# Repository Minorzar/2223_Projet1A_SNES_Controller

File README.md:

# SNES Project (Controller)

This is the repository of the SNES project carried out at ENSEA by the promotion of 2025.

In the first year, as part of a three-month project, we will attempt to create our own version of the SNES controller. The aim will be to complete the controller ourselves, both in terms of hardware and software, while adding features that were not present on the original controller. However, this is only the first part of our SNES project, as we'll be continuing the project next year, this time focusing on the console itself. As such, this repository will probably only contain files relevant to the controller.

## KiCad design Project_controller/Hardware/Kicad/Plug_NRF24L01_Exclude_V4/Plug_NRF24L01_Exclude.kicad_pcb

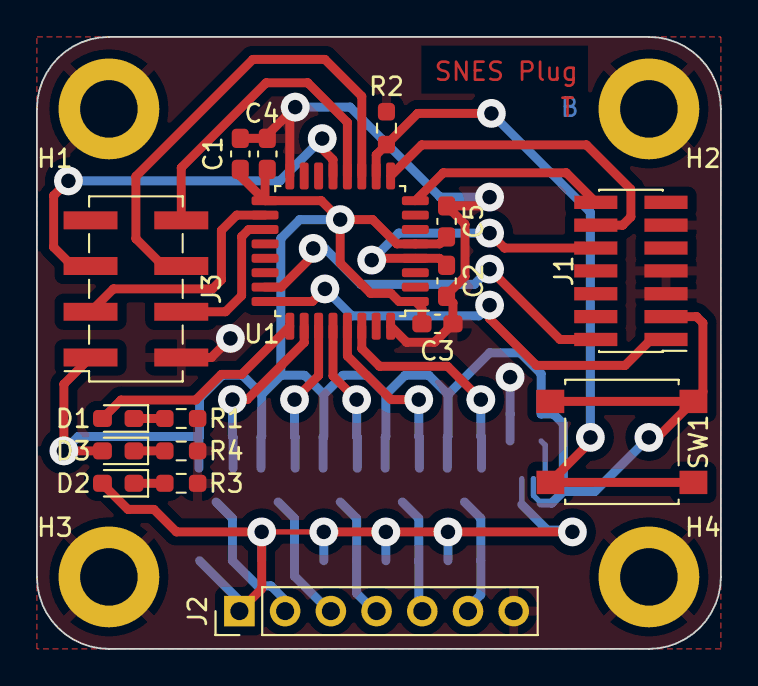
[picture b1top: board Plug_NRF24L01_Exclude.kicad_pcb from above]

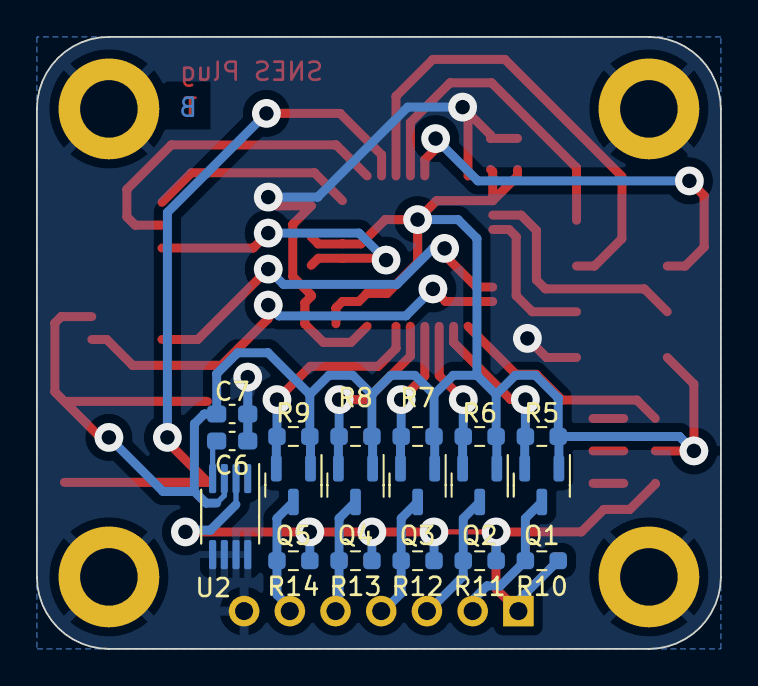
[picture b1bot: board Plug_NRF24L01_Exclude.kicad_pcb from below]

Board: 2 copper layers, 38.0 x 34.0 mm, 39 parts (18 on the bottom side), 29 nets.

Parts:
C1: 10u; C_0603_1608Metric_Pad1.08x0.95mm_HandSolder
C2, C3, C4, C5: 100n; C_0603_1608Metric_Pad1.08x0.95mm_HandSolder
C6: 470p; C_0603_1608Metric_Pad1.08x0.95mm_HandSolder
C7: 2.2u; C_0603_1608Metric_Pad1.08x0.95mm_HandSolder
D1, D2: LED_Small; D_0603_1608Metric_Pad1.05x0.95mm_HandSolder
D3: LED; D_0603_1608Metric_Pad1.05x0.95mm_HandSolder
H1, H2, H3, H4: MountingHole_Pad; MountingHole_3.2mm_M3_DIN965_Pad
J1: Conn_02x07_Odd_Even; PinHeader_2x07_P1.27mm_Vertical_SMD
J2: Conn_01x07_Socket; PinHeader_1x07_P2.54mm_Vertical
J3: Conn_01x08_Socket; PinSocket_2x04_P2.54mm_Vertical_SMD
Q1, Q2, Q3, Q4, Q5: 2N7002; SOT-23
R1, R3, R4: 1k; R_0603_1608Metric_Pad0.98x0.95mm_HandSolder
R2, R5, R6, R7, R8, R9, R10, R11, R12, R13, R14: 10k; R_0603_1608Metric_Pad0.98x0.95mm_HandSolder
SW1: SW_SPST; SW_SPST_B3S-1000
U1: STM32L412KBTx; LQFP-32_7x7mm_P0.8mm
U2: MIC5219-3.3YMM; MSOP-8_3x3mm_P0.65mm

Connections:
+3.3V: C1.1, C3.1, C4.1, C5.1, C7.1, D3.2 (A), J1.3, J3.1, Q1.1 (G), Q2.1 (G), Q3.1 (G), Q4.1 (G), Q5.1 (G), R5.1, R6.1, R7.1, R8.1, R9.1, SW1.2 (B), U1.1 (VDD), U1.5 (VDDA), U1.17 (VDD), U2.3 (OUT)
+5V: D2.2 (A), J2.1, R10.1, R11.1, R12.1, R13.1, R14.1, U2.2 (IN)
Appairing_Btn: R2.1, SW1.1 (A), U1.10 (PA4)
Chip_Enable: J3.4, U1.19 (PA9)
Data_Clock_SNES: J2.2, Q1.3 (D), R10.2
Data_Clock_STM32: Q1.2 (S), R5.2, U1.26 (PB3)
Data_Latch_SNES: J2.3, Q2.3 (D), R11.2
Data_Latch_STM32: Q2.2 (S), R6.2, U1.27 (PB4)
GND: C1.2, C2.1, C3.2, C4.2, C5.2, C6.2, C7.2, H1.1, H2.1, H3.1, H4.1, J1.5, J1.7, J1.11, J2.7, J3.2, R1.2, R2.2, R3.2, R4.2, U1.16 (VSS), U1.32 (VSS), U2.5 (GND), U2.6 (GND), U2.7 (GND), U2.8 (GND)
IOBit_SNES: J2.6, Q5.3 (D), R14.2
IOBit_STM32: Q5.2 (S), R9.2, U1.30 (PB7)
NRST: C2.2, J1.10, U1.4 (NRST)
unnamed: D1.1 (K), R1.1
unnamed: D2.1 (K), R3.1
unnamed: D3.1 (K), R4.1
unnamed: C6.1, U2.4 (BP)
SPI_Chip_Select: J3.3, U1.18 (PA8)
SPI_Clock: J3.6, U1.11 (PA5)
SPI_Digital_Input: J3.8, U1.12 (PA6)
SPI_Digital_Output: J3.5, U1.13 (PA7)
SWDCK: J1.1, U1.24 (PA14)
SWDIO: J1.2, U1.23 (PA13)
Serial_Data1_SNES: J2.4, Q3.3 (D), R12.2
Serial_Data1_STM32: Q3.2 (S), R7.2, U1.28 (PB5)
Serial_Data2_SNES: J2.5, Q4.3 (D), R13.2
Serial_Data2_STM32: Q4.2 (S), R8.2, U1.29 (PB6)
Status_LED: D1.2 (A), U1.25 (PA15)
USART2_RX: J1.12, U1.9 (PA3)
USART2_TX: J1.14, U1.8 (PA2)

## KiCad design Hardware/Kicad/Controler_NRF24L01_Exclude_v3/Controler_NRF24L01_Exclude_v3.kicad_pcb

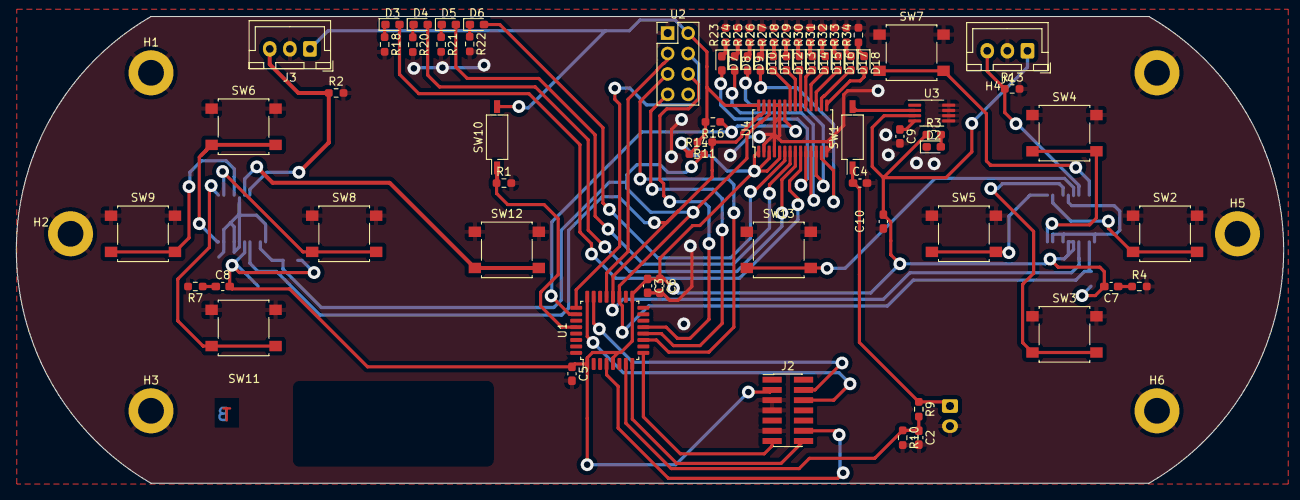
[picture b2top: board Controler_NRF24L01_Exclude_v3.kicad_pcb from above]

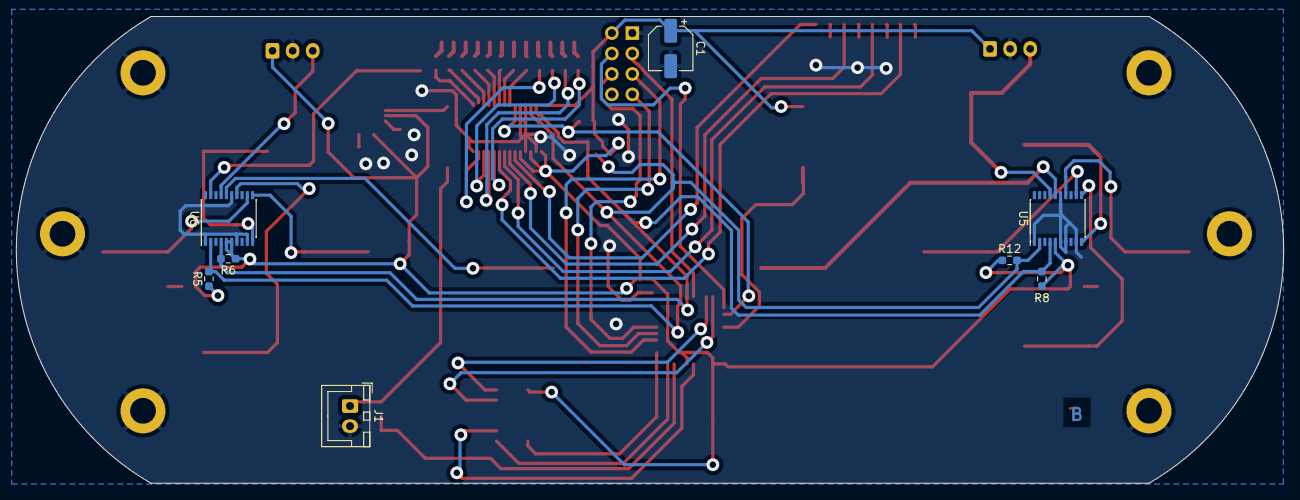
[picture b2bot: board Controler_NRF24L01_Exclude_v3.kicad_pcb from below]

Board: 2 copper layers, 157.4 x 58.0 mm, 87 parts (8 on the bottom side), 68 nets.

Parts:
C1: 22uF; CP_Elec_5x5.4
C2: 1nF; C_0603_1608Metric_Pad1.08x0.95mm_HandSolder
C3, C5: 100n; C_0603_1608Metric_Pad1.08x0.95mm_HandSolder
C4: 1u; C_0603_1608Metric_Pad1.08x0.95mm_HandSolder
C6: 10u; C_0603_1608Metric_Pad1.08x0.95mm_HandSolder
C7, C8, C10: 100nF; C_0603_1608Metric_Pad1.08x0.95mm_HandSolder
C9: 470p; C_0603_1608Metric_Pad1.08x0.95mm_HandSolder
D2: LED_Small; LED_0603_1608Metric_Pad1.05x0.95mm_HandSolder
D3: G1; LED_0603_1608Metric_Pad1.05x0.95mm_HandSolder
D4: G2; LED_0603_1608Metric_Pad1.05x0.95mm_HandSolder
D5: G3; LED_0603_1608Metric_Pad1.05x0.95mm_HandSolder
D6: G4; LED_0603_1608Metric_Pad1.05x0.95mm_HandSolder
D7: G5; LED_0603_1608Metric_Pad1.05x0.95mm_HandSolder
D8: G6; LED_0603_1608Metric_Pad1.05x0.95mm_HandSolder
D9: G7; LED_0603_1608Metric_Pad1.05x0.95mm_HandSolder
D10: G8; LED_0603_1608Metric_Pad1.05x0.95mm_HandSolder
D11: O1; LED_0603_1608Metric_Pad1.05x0.95mm_HandSolder
D12: O2; LED_0603_1608Metric_Pad1.05x0.95mm_HandSolder
D13: O3; LED_0603_1608Metric_Pad1.05x0.95mm_HandSolder
D14: O4; LED_0603_1608Metric_Pad1.05x0.95mm_HandSolder
D15: R1; LED_0603_1608Metric_Pad1.05x0.95mm_HandSolder
D16: R2; LED_0603_1608Metric_Pad1.05x0.95mm_HandSolder
D17: R3; LED_0603_1608Metric_Pad1.05x0.95mm_HandSolder
D18: R4; LED_0603_1608Metric_Pad1.05x0.95mm_HandSolder
H1, H2, H3, H4, H5, H6: MountingHole_Pad; MountingHole_3.2mm_M3_DIN965_Pad
J1: Conn_01x02; JST_XH_B2B-XH-A_1x02_P2.50mm_Vertical
J2: Conn_02x07_Odd_Even; PinHeader_2x07_P1.27mm_Vertical_SMD
J3, J4: Conn_01x03; JST_XH_B3B-XH-A_1x03_P2.50mm_Vertical
R1, R2, R3, R13, R18, R20, R21, R22, R23, R24, R25, R26, R27, R28, R29, R30, R31, R32, R33, R34: 1K; R_0603_1608Metric_Pad0.98x0.95mm_HandSolder
R4, R7: 1k; R_0603_1608Metric_Pad0.98x0.95mm_HandSolder
R5, R6, R8, R11, R12, R14, R16: 10K; R_0603_1608Metric_Pad0.98x0.95mm_HandSolder
R9, R10: 1M; R_0603_1608Metric_Pad0.98x0.95mm_HandSolder
SW1, SW10: SW_DIP_x01; SW_DIP_SPSTx01_Slide_Copal_CHS-01B_W7.62mm_P1.27mm
SW2, SW3, SW4, SW5, SW6, SW8, SW9, SW11, SW12, SW13: SW_Push; SW_SPST_B3S-1000
SW7: SW_SPST; SW_SPST_B3S-1000
U1: STM32L412KBTx; LQFP-32_7x7mm_P0.8mm
U2: nRF24_Full; PinHeader_2x04_P2.54mm_Vertical
U3: MIC5219-3.3YMM; MSOP-8_3x3mm_P0.65mm
U4: PCA9685PW; TSSOP-28_4.4x9.7mm_P0.65mm
U5, U6: PCF8574TS; SSOP-20_4.4x6.5mm_P0.65mm

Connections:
A_Button: SW2.2, U6.12 (P2)
B_Button: SW3.2, U6.14 (P3)
CSN_nRF24: U1.25 (PA15), U2.4 (CSN)
DC_Button: SW11.2, U5.11 (P1)
DIODE_OE: R16.1, U1.26 (PB3), U4.23 (~OE)
DIO/EX_CLK: R5.2, R12.2, R14.2, U1.19 (PA9), U4.26 (SCL), U5.2 (SCL), U6.2 (SCL)
DIO/EX_SDA: R6.2, R8.2, R11.1, U1.20 (PA10), U4.27 (SDA), U5.4 (SDA), U6.4 (SDA)
Digital_Out_Put: U1.12 (PA6), U2.7 (MISO)
GND: C1.2, C2.2, C3.2, C4.2, C5.2, C6.2, C9.2, C10.2, D2.1 (K), H1.1, H2.1, H3.1, H4.1, H5.1, H6.1, J1.2, J2.5, J2.7, J2.11, J3.2, J4.2, R1.2, R2.2, R4.2, R7.2, R10.2, R13.2, R18.2, R20.2, R21.2, R22.2, R23.2, R24.2, R25.2, R26.2, R27.2, R28.2, R29.2, R30.2, R31.2, R32.2, R33.2, R34.2, SW2.1, SW3.1, SW4.1, SW5.1, SW6.1, SW7.1 (A), SW8.1, SW9.1, SW11.1, SW12.1, SW13.1, U1.16 (VSS), U1.32 (VSS), U2.1 (GND), U3.5 (GND), U3.6 (GND), U3.7 (GND), U3.8 (GND), U4.2 (A1), U4.4 (A3), U4.14 (VSS), U4.24 (A5), U4.25 (EXTCLK), U5.1 (~INT), U5.6 (A0), U5.7 (A1), U5.9 (A2), U5.15 (VSS), U6.1 (~INT), U6.7 (A1), U6.9 (A2), U6.15 (VSS)
Glob_Alim: C1.1, C3.1, C5.1, C6.1, C7.2, C8.2, C10.1, J2.3, J3.1, J4.1, R3.1, R5.1, R6.1, R8.1, R11.2, R12.1, R14.1, R16.2, SW10.2, U1.1 (VDD), U1.5 (VDDA), U1.17 (VDD), U2.2 (VCC), U3.3 (OUT), U4.1 (A0), U4.3 (A2), U4.5 (A4), U4.28 (VDD), U5.5 (VDD), U6.5 (VDD), U6.6 (A0)
L: J4.3, R13.1, U6.17 (P5)
LC_Button: SW8.2, U5.12 (P2)
Li-ion: C4.1, J1.1, R9.1, SW1.1
MOSI: U1.13 (PA7), U2.6 (MOSI)
NES/SNES_switcher: R1.1, SW10.1, U1.28 (PB5)
unnamed: SW1.2, U3.2 (IN)
unnamed: C7.1, R4.1
unnamed: C8.1, R7.1
unnamed: D2.2 (A), R3.2
unnamed: D3.2 (A), U4.9 (LED3)
unnamed: D3.1 (K), R18.1
unnamed: D4.2 (A), U4.8 (LED2)
unnamed: D4.1 (K), R20.1
unnamed: D5.2 (A), U4.7 (LED1)
unnamed: D5.1 (K), R21.1
unnamed: D6.2 (A), U4.6 (LED0)
unnamed: D6.1 (K), R22.1
unnamed: D7.2 (A), U4.10 (LED4)
unnamed: D7.1 (K), R23.1
unnamed: D8.2 (A), U4.11 (LED5)
unnamed: D8.1 (K), R24.1
unnamed: D9.2 (A), U4.12 (LED6)
unnamed: D9.1 (K), R25.1
unnamed: D10.2 (A), U4.13 (LED7)
unnamed: D10.1 (K), R26.1
unnamed: D11.2 (A), U4.22 (LED15)
unnamed: D11.1 (K), R27.1
unnamed: D12.2 (A), U4.21 (LED14)
unnamed: D12.1 (K), R28.1
unnamed: D13.2 (A), U4.20 (LED13)
unnamed: D13.1 (K), R29.1
unnamed: D14.2 (A), U4.19 (LED12)
unnamed: D14.1 (K), R30.1
unnamed: D15.2 (A), U4.18 (LED11)
unnamed: D15.1 (K), R31.1
unnamed: D16.2 (A), U4.17 (LED10)
unnamed: D16.1 (K), R32.1
unnamed: D17.2 (A), U4.16 (LED9)
unnamed: D17.1 (K), R33.1
unnamed: D18.2 (A), U4.15 (LED8)
unnamed: D18.1 (K), R34.1
unnamed: C9.1, U3.4 (BP)
Order_Search: SW7.2 (B), U6.19 (P6)
POWER_CHECK: C2.1, R9.2, R10.1, U1.7 (PA1)
Pin_Clock: U1.11 (PA5), U2.5 (SCK)
R: J3.3, R2.1, U5.17 (P5)
RC_Button: SW9.2, U5.14 (P3)
RX/TX: U1.21 (PA11), U2.3 (CE)
Reset_Buton: J2.12, U1.4 (NRST)
SE_Button: SW13.2, U6.16 (P4)
ST_Button: SW12.2, U5.16 (P4)
SWDCK: J2.6, U1.24 (PA14)
SWDIO: J2.4, U1.23 (PA13)
UC_Button: SW6.2, U5.10 (P0)
USART2_RX: J2.13, U1.9 (PA3)
USART2_TX: J2.14, U1.8 (PA2)
X_Button: SW4.2, U6.10 (P0)
Y_Button: SW5.2, U6.11 (P1)

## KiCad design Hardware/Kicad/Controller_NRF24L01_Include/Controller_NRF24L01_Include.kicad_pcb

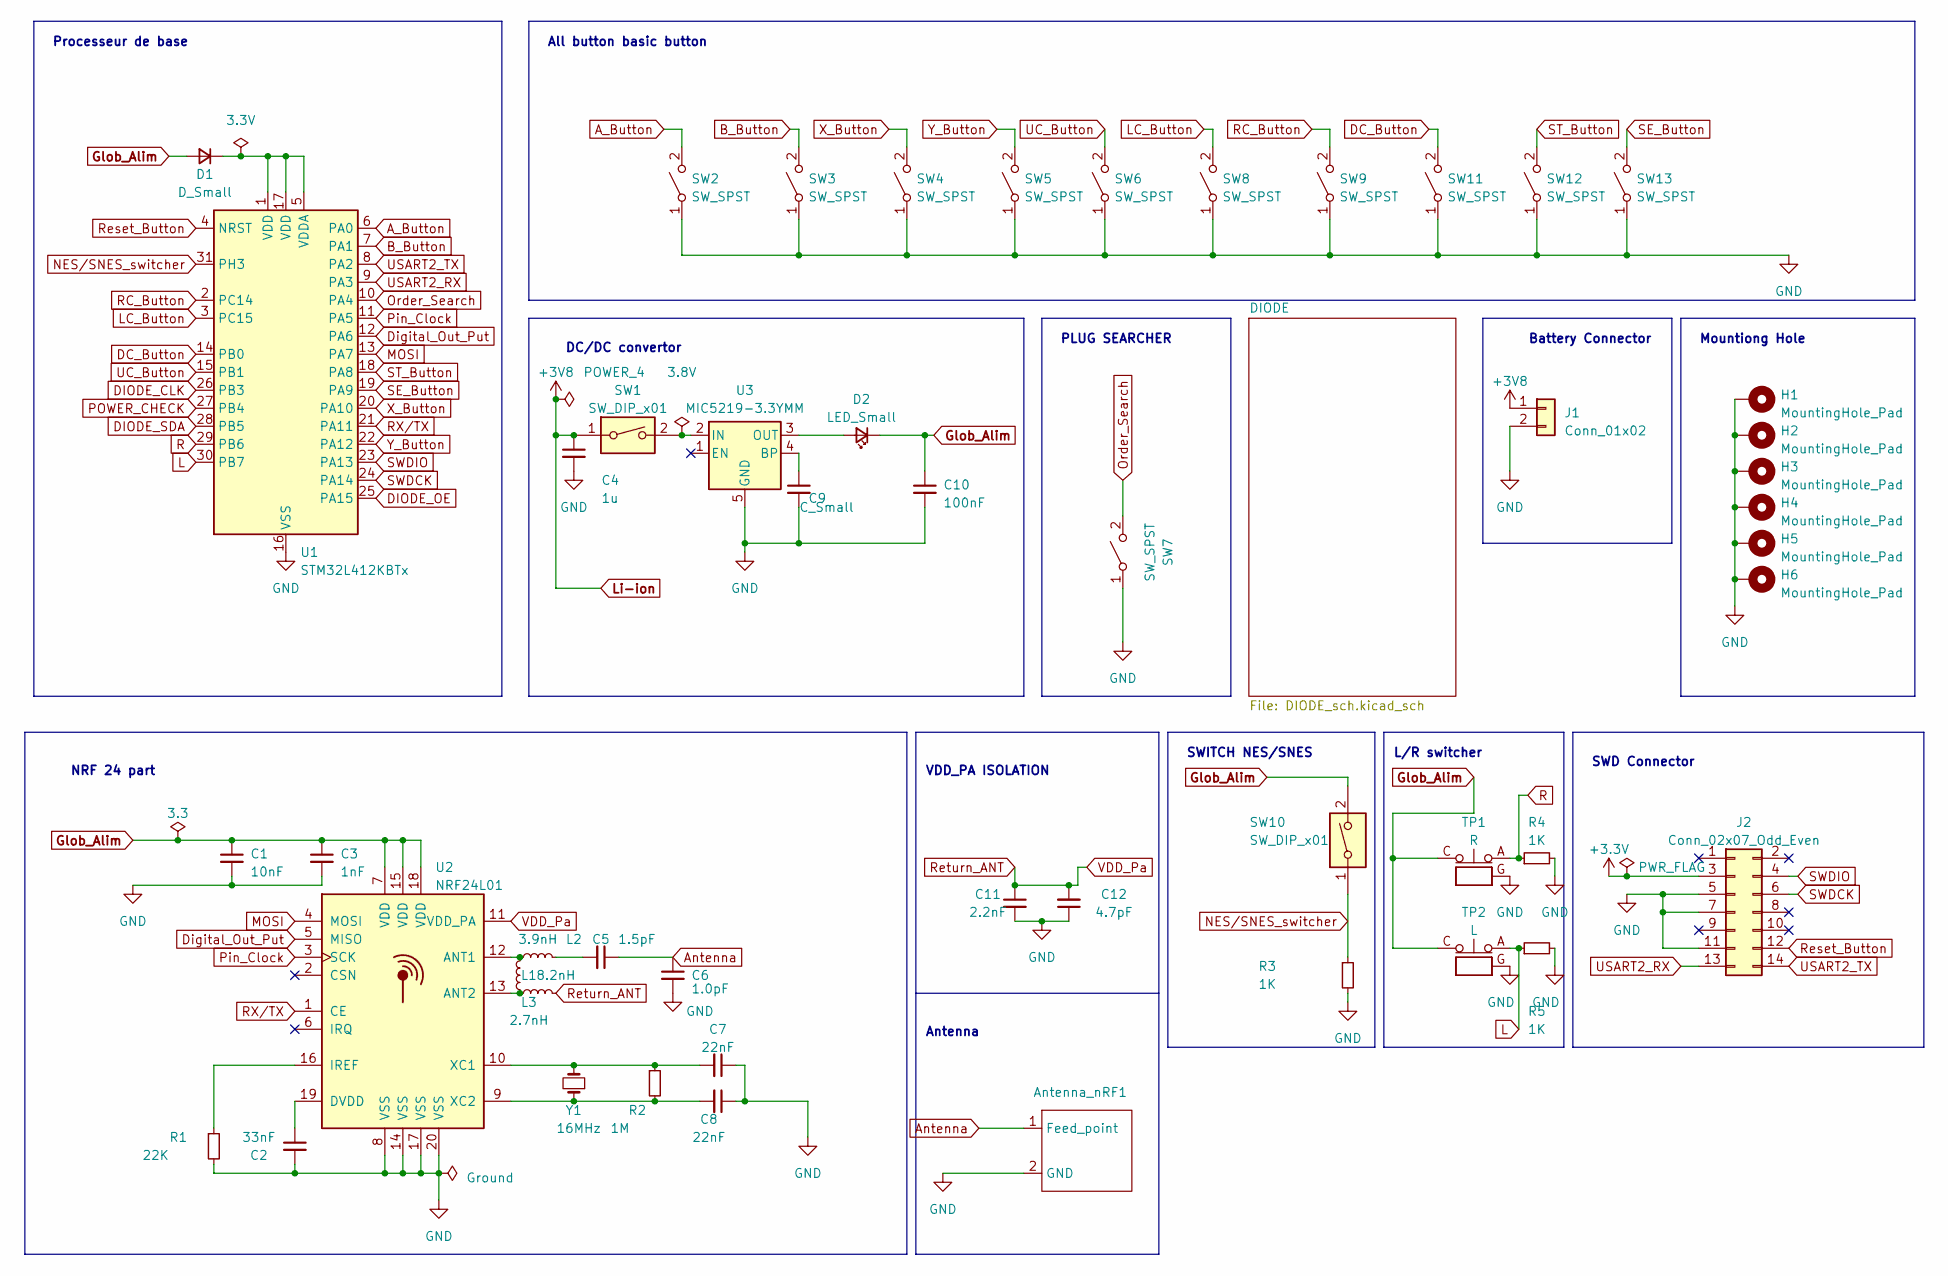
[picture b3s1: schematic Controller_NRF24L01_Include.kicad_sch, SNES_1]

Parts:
Antenna_nRF1: Texas_SWRA117D_2.4GHz_Right
C1: 10nF; C_0603_1608Metric_Pad1.08x0.95mm_HandSolder
C2: 33nF; C_0603_1608Metric_Pad1.08x0.95mm_HandSolder
C3: 1nF; C_0603_1608Metric_Pad1.08x0.95mm_HandSolder
C4: 1u; C_0603_1608Metric_Pad1.08x0.95mm_HandSolder
C5: 1.5pF; C_0402_1005Metric_Pad0.74x0.62mm_HandSolder
C6: 1.0pF; C_0402_1005Metric_Pad0.74x0.62mm_HandSolder
C7, C8: 22nF; C_0603_1608Metric_Pad1.08x0.95mm_HandSolder
C9: C_Small; C_0603_1608Metric_Pad1.08x0.95mm_HandSolder
C10: 100nF; C_0603_1608Metric_Pad1.08x0.95mm_HandSolder
C11: 2.2nF; C_0402_1005Metric_Pad0.74x0.62mm_HandSolder
C12: 4.7pF; C_0402_1005Metric_Pad0.74x0.62mm_HandSolder
D1: D_Small; D_0603_1608Metric_Pad1.05x0.95mm_HandSolder
D2: LED_Small; LED_0603_1608Metric_Pad1.05x0.95mm_HandSolder
H1, H2, H3, H4, H5, H6: MountingHole_Pad; MountingHole_3.2mm_M3_DIN965_Pad
J1: Conn_01x02; JST_XH_B2B-XH-A_1x02_P2.50mm_Vertical
J2: Conn_02x07_Odd_Even; PinHeader_2x07_P1.27mm_Vertical_SMD
L1: 8.2nH; L_0603_1608Metric_Pad1.05x0.95mm_HandSolder
L2: 3.9nH; L_0603_1608Metric_Pad1.05x0.95mm_HandSolder
L3: 2.7nH; L_0402_1005Metric_Pad0.77x0.64mm_HandSolder
R1: 22K; R_0603_1608Metric_Pad0.98x0.95mm_HandSolder
R2: 1M; R_0603_1608Metric_Pad0.98x0.95mm_HandSolder
R3, R4, R5: 1K; R_0603_1608Metric_Pad0.98x0.95mm_HandSolder
SW1, SW10: SW_DIP_x01; SW_DIP_SPSTx01_Slide_Copal_CHS-01B_W7.62mm_P1.27mm
SW2, SW3, SW4, SW5, SW6, SW7, SW8, SW9, SW11, SW12, SW13: SW_SPST; SW_SPST_B3S-1000
TP1: R; SMA_Molex_73251-1153_EdgeMount_Horizontal
TP2: L; SMA_Molex_73251-1153_EdgeMount_Horizontal
U1: STM32L412KBTx; LQFP-32_7x7mm_P0.8mm
U2: NRF24L01; QFN-20-1EP_4x4mm_P0.5mm_EP2.5x2.5mm
U3: MIC5219-3.3YMM; MSOP-8_3x3mm_P0.65mm
Y1: 16MHz; Crystal_SMD_HC49-SD_HandSoldering

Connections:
+3.3V: J2.3
A_Button: SW2.2 (B), U1.6 (PA0)
Antenna: Antenna_nRF1.1 (Feed_point), C5.1, C6.1
B_Button: SW3.2 (B), U1.7 (PA1)
DC_Button: SW11.2 (B), U1.14 (PB0)
DIODE_CLK: U1.26 (PB3); also elsewhere on the board
DIODE_OE: U1.25 (PA15); also elsewhere on the board
DIODE_SDA: U1.28 (PB5); also elsewhere on the board
Digital_Out_Put: U1.12 (PA6), U2.5 (MISO)
GND: Antenna_nRF1.2 (GND), C1.2, C2.2, C3.2, C4.2, C6.2, C7.1, C8.1, C9.2, C10.2, C11.2, C12.1, H1.1, H2.1, H3.1, H4.1, H5.1, H6.1, J1.2, J2.5, J2.7, J2.11, R1.2, R3.2, R4.2, R5.2, SW2.1 (A), SW3.1 (A), SW4.1 (A), SW5.1 (A), SW6.1 (A), SW7.1 (A), SW8.1 (A), SW9.1 (A), SW11.1 (A), SW12.1 (A), SW13.1 (A), TP1.G, TP2.G, U1.16 (VSS), U1.32 (VSS), U2.8 (VSS), U2.14 (VSS), U2.17 (VSS), U2.20 (VSS), U3.5 (GND), U3.6 (GND), U3.7 (GND), U3.8 (GND); also elsewhere on the board
Glob_Alim: C1.1, C3.1, C10.1, D1.2 (A), D2.1 (K), SW10.2, TP1.C, TP2.C, U2.7 (VDD), U2.15 (VDD), U2.18 (VDD); also elsewhere on the board
L: R5.1, TP2.A, U1.30 (PB7)
LC_Button: SW8.2 (B), U1.3 (PC15)
Li-ion: C4.1, J1.1, SW1.1; also elsewhere on the board
MOSI: U1.13 (PA7), U2.4 (MOSI)
NES/SNES_switcher: R3.1, SW10.1, U1.31 (PH3)
unnamed: D1.1 (K), U1.1 (VDD), U1.5 (VDDA), U1.17 (VDD)
unnamed: SW1.2, U3.2 (IN)
unnamed: C5.2, L2.2
unnamed: D2.2 (A), U3.3 (OUT)
unnamed: L1.2, L2.1, U2.12 (ANT1)
unnamed: L1.1, L3.1, U2.13 (ANT2)
unnamed: C2.1, U2.19 (DVDD)
unnamed: R1.1, U2.16 (IREF)
unnamed: C7.2, R2.1, U2.10 (XC1), Y1.2
unnamed: C8.2, R2.2, U2.9 (XC2), Y1.1
unnamed: C9.1, U3.4 (BP)
Order_Search: SW7.2 (B), U1.10 (PA4)
POWER_CHECK: U1.27 (PB4); also elsewhere on the board
Pin_Clock: U1.11 (PA5), U2.3 (SCK)
R: R4.1, TP1.A, U1.29 (PB6)
RC_Button: SW9.2 (B), U1.2 (PC14)
RX/TX: U1.21 (PA11), U2.1 (CE)
Reset_Button: J2.12, U1.4 (NRST)
Return_ANT: C11.1, C12.2, L3.2, U2.11 (VDD_PA)
SE_Button: SW13.2 (B), U1.19 (PA9)
ST_Button: SW12.2 (B), U1.18 (PA8)
SWDCK: J2.6, U1.24 (PA14)
SWDIO: J2.4, U1.23 (PA13)
UC_Button: SW6.2 (B), U1.15 (PB1)
USART2_RX: J2.13, U1.9 (PA3)
USART2_TX: J2.14, U1.8 (PA2)
X_Button: SW4.2 (B), U1.20 (PA10)
Y_Button: SW5.2 (B), U1.22 (PA12)

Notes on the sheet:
L/R switcher
NRF 24 part
Antenna
Mountiong Hole
Processeur de base
PLUG SEARCHER
VDD_PA ISOLATION
All button basic button
Battery Connector
DC/DC convertor
SWD Connector
SWITCH NES/SNES

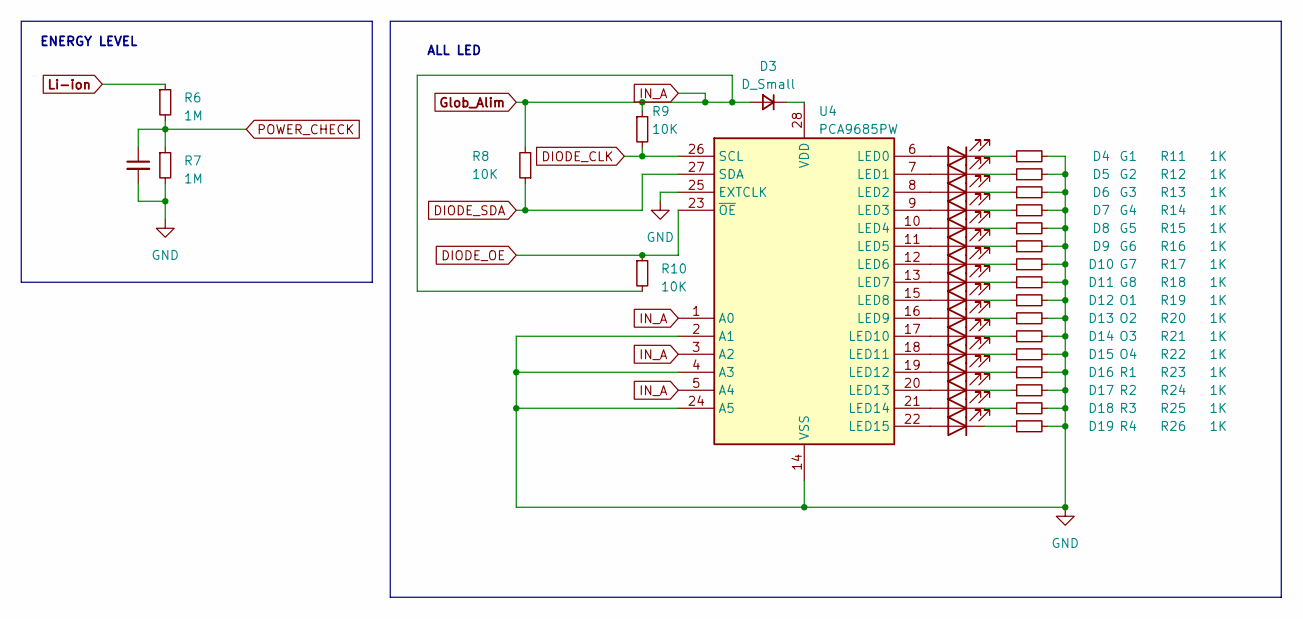
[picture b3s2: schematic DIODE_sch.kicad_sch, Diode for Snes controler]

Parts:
C13: 1nF; C_0603_1608Metric_Pad1.08x0.95mm_HandSolder
D3: D_Small; HDSP-4832
D4: G1; LED_0603_1608Metric_Pad1.05x0.95mm_HandSolder
D5: G2; LED_0603_1608Metric_Pad1.05x0.95mm_HandSolder
D6: G3; LED_0603_1608Metric_Pad1.05x0.95mm_HandSolder
D7: G4; LED_0603_1608Metric_Pad1.05x0.95mm_HandSolder
D8: G5; LED_0603_1608Metric_Pad1.05x0.95mm_HandSolder
D9: G6; LED_0603_1608Metric_Pad1.05x0.95mm_HandSolder
D10: G7; LED_0603_1608Metric_Pad1.05x0.95mm_HandSolder
D11: G8; LED_0603_1608Metric_Pad1.05x0.95mm_HandSolder
D12: O1; LED_0603_1608Metric_Pad1.05x0.95mm_HandSolder
D13: O2; LED_0603_1608Metric_Pad1.05x0.95mm_HandSolder
D14: O3; LED_0603_1608Metric_Pad1.05x0.95mm_HandSolder
D15: O4; LED_0603_1608Metric_Pad1.05x0.95mm_HandSolder
D16: R1; LED_0603_1608Metric_Pad1.05x0.95mm_HandSolder
D17: R2; LED_0603_1608Metric_Pad1.05x0.95mm_HandSolder
D18: R3; LED_0603_1608Metric_Pad1.05x0.95mm_HandSolder
D19: R4; LED_0603_1608Metric_Pad1.05x0.95mm_HandSolder
R6, R7: 1M; R_0603_1608Metric_Pad0.98x0.95mm_HandSolder
R8, R9, R10: 10K; R_0603_1608Metric_Pad0.98x0.95mm_HandSolder
R11, R12, R13, R14, R15, R16, R17, R18, R19, R20, R21, R22, R23, R24, R25, R26: 1K; R_0603_1608Metric_Pad0.98x0.95mm_HandSolder
U4: PCA9685PW; TSSOP-28_4.4x9.7mm_P0.65mm

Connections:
DIODE_CLK: R9.2, U4.26 (SCL); also elsewhere on the board
DIODE_OE: R10.1, U4.23 (~OE); also elsewhere on the board
DIODE_SDA: R8.1, U4.27 (SDA); also elsewhere on the board
GND: C13.2, R7.2, R11.2, R12.2, R13.2, R14.2, R15.2, R16.2, R17.2, R18.2, R19.2, R20.2, R21.2, R22.2, R23.2, R24.2, R25.2, R26.2, U4.2 (A1), U4.4 (A3), U4.14 (VSS), U4.24 (A5), U4.25 (EXTCLK); also elsewhere on the board
Glob_Alim: D3.2 (A), R8.2, R9.1, R10.2, U4.1 (A0), U4.3 (A2), U4.5 (A4); also elsewhere on the board
Li-ion: R6.1; also elsewhere on the board
unnamed: D3.1 (K), U4.28 (VDD)
unnamed: D4.2 (A), U4.6 (LED0)
unnamed: D4.1 (K), R11.1
unnamed: D5.2 (A), U4.7 (LED1)
unnamed: D5.1 (K), R12.1
unnamed: D6.2 (A), U4.8 (LED2)
unnamed: D6.1 (K), R13.1
unnamed: D7.2 (A), U4.9 (LED3)
unnamed: D7.1 (K), R14.1
unnamed: D8.2 (A), U4.10 (LED4)
unnamed: D8.1 (K), R15.1
unnamed: D9.2 (A), U4.11 (LED5)
unnamed: D9.1 (K), R16.1
unnamed: D10.2 (A), U4.12 (LED6)
unnamed: D10.1 (K), R17.1
unnamed: D11.2 (A), U4.13 (LED7)
unnamed: D11.1 (K), R18.1
unnamed: D12.2 (A), U4.15 (LED8)
unnamed: D12.1 (K), R19.1
unnamed: D13.2 (A), U4.16 (LED9)
unnamed: D13.1 (K), R20.1
unnamed: D14.2 (A), U4.17 (LED10)
unnamed: D14.1 (K), R21.1
unnamed: D15.2 (A), U4.18 (LED11)
unnamed: D15.1 (K), R22.1
unnamed: D16.2 (A), U4.19 (LED12)
unnamed: D16.1 (K), R23.1
unnamed: D17.2 (A), U4.20 (LED13)
unnamed: D17.1 (K), R24.1
unnamed: D18.2 (A), U4.21 (LED14)
unnamed: D18.1 (K), R25.1
unnamed: D19.2 (A), U4.22 (LED15)
unnamed: D19.1 (K), R26.1
POWER_CHECK: C13.1, R6.2, R7.1; also elsewhere on the board

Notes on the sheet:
ALL LED
ENERGY LEVEL

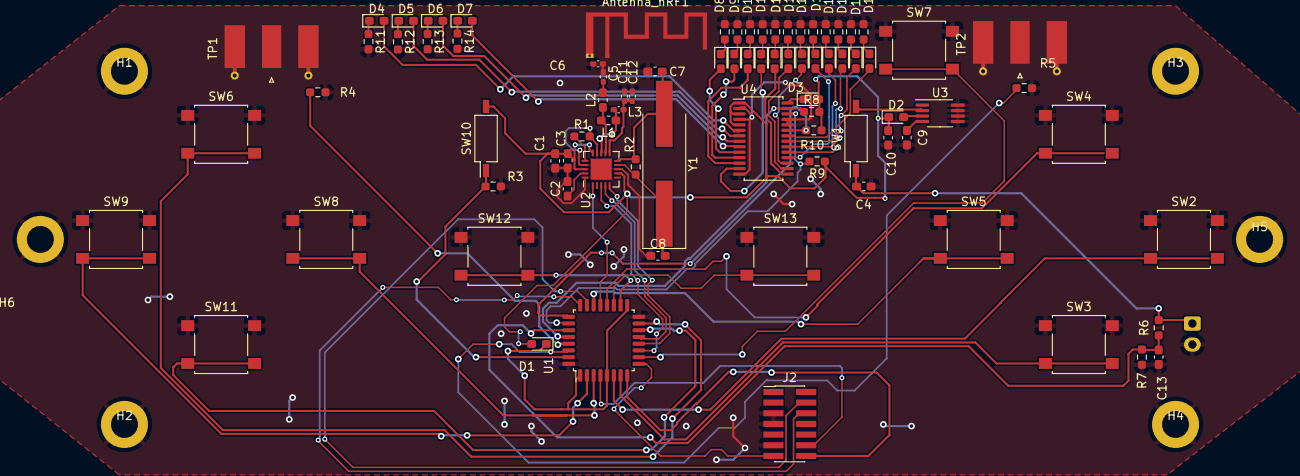
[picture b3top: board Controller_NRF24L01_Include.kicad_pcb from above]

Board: 2 copper layers, 90 parts (1 on the bottom side), 76 nets.

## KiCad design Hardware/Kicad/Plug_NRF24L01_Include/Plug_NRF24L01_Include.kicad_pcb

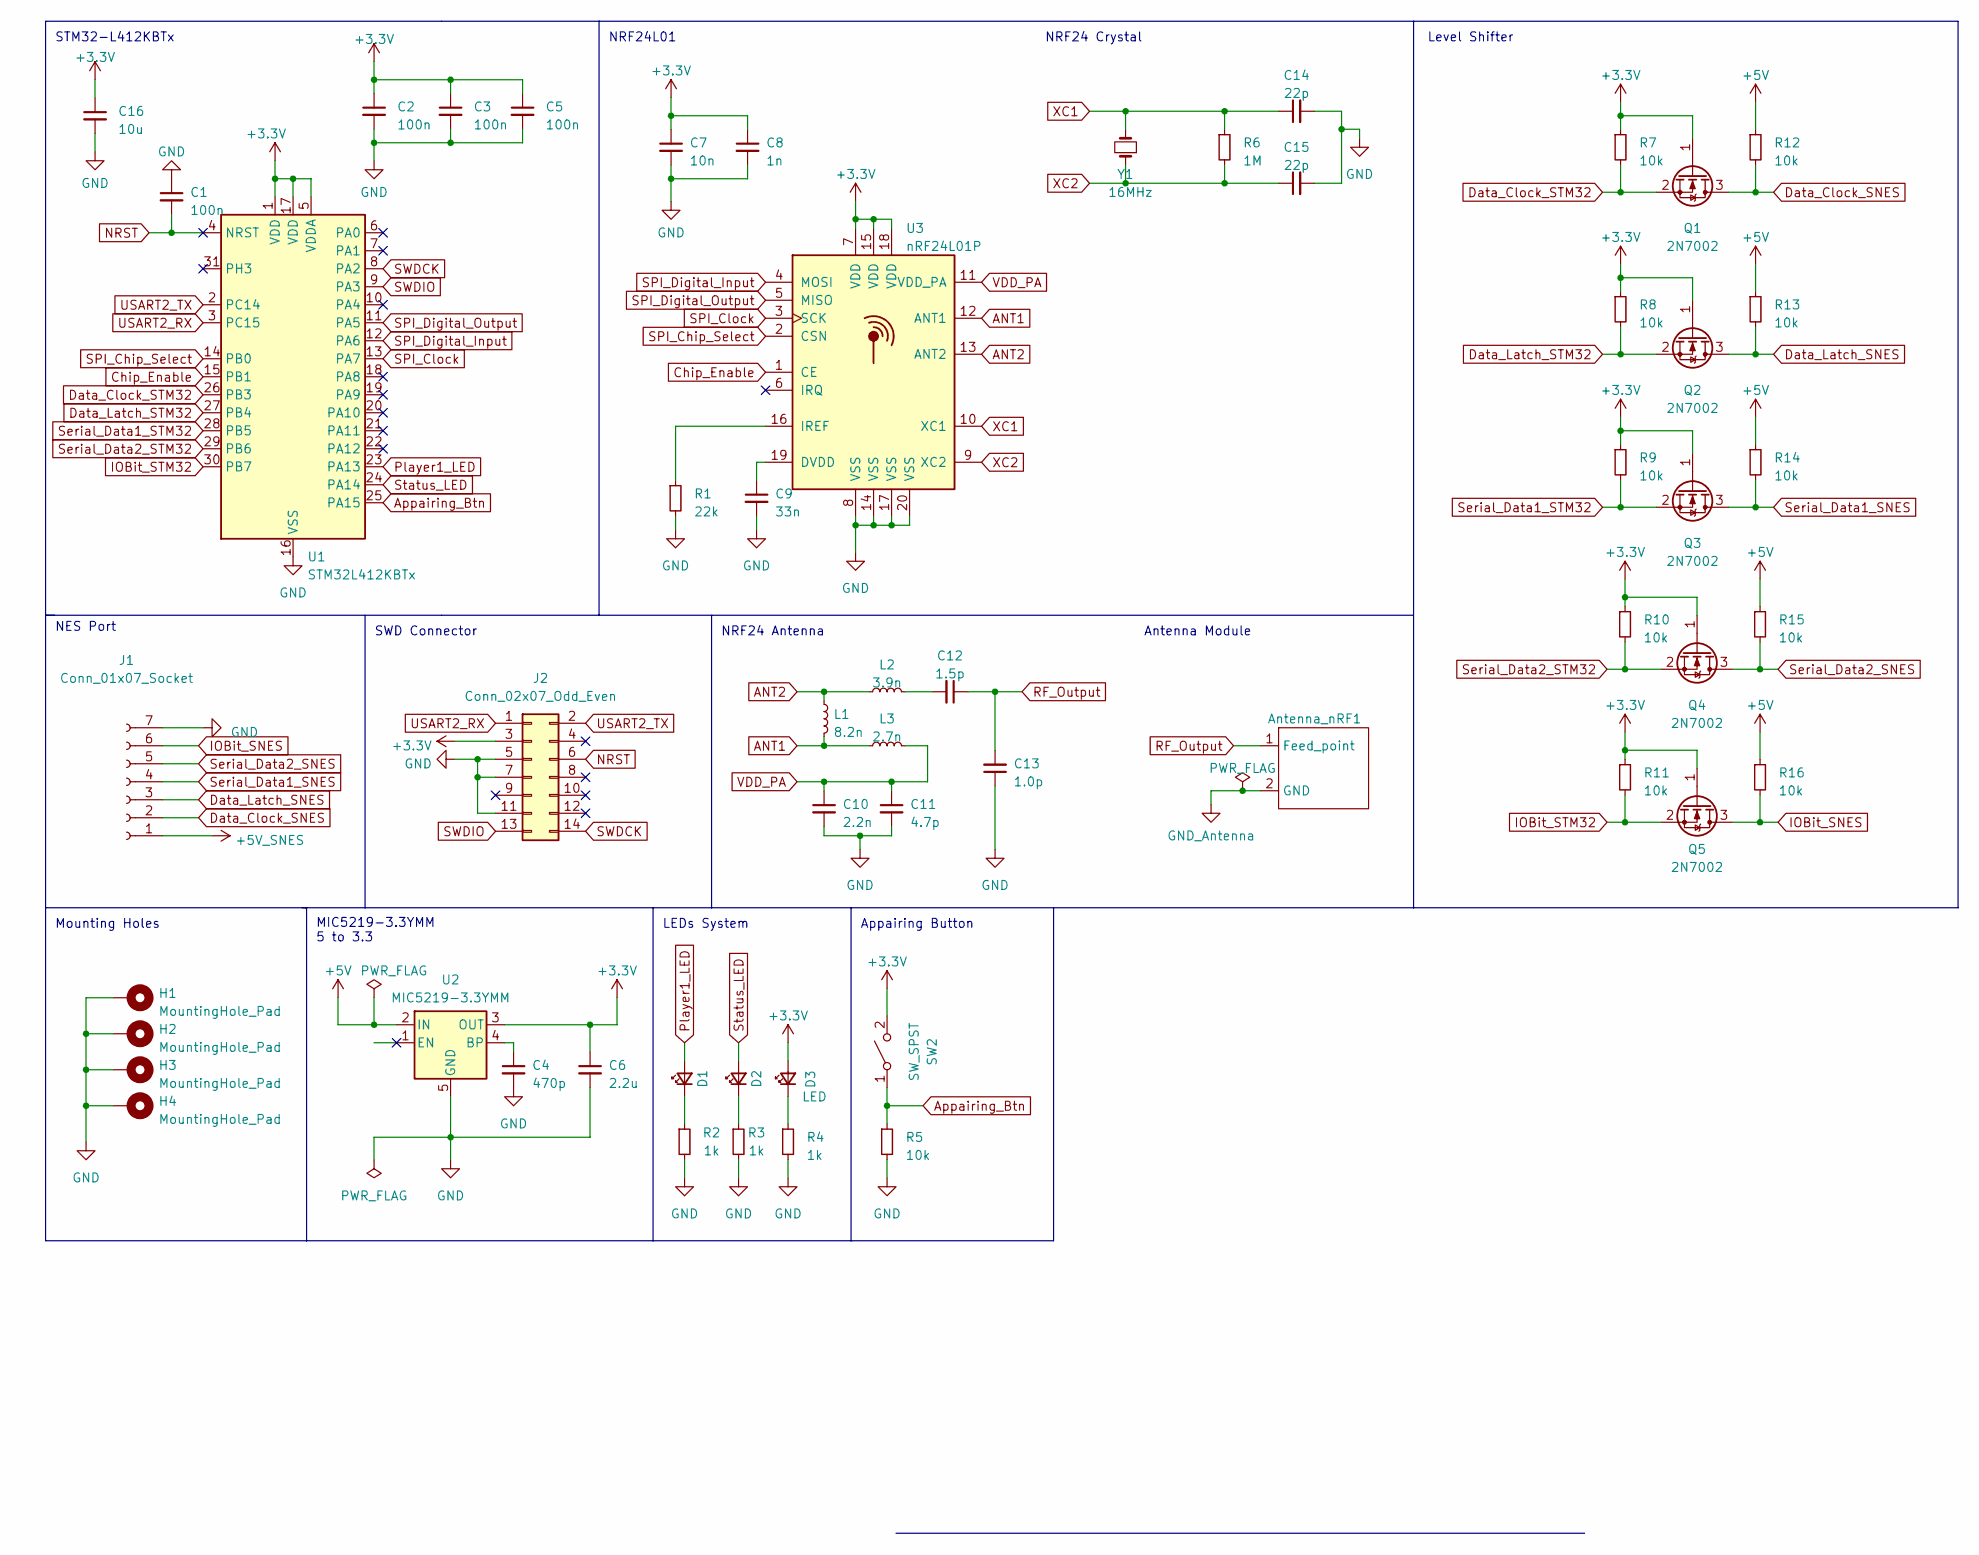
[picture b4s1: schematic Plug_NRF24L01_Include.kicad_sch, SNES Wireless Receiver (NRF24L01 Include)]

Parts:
Antenna_nRF1: Texas_SWRA117D_2.4GHz_Right
C1, C2, C3, C5: 100n; C_0603_1608Metric_Pad1.08x0.95mm_HandSolder
C4: 470p; C_0603_1608Metric_Pad1.08x0.95mm_HandSolder
C6: 2.2u; C_0603_1608Metric_Pad1.08x0.95mm_HandSolder
C7: 10n; C_0603_1608Metric_Pad1.08x0.95mm_HandSolder
C8: 1n; C_0603_1608Metric_Pad1.08x0.95mm_HandSolder
C9: 33n; C_0603_1608Metric_Pad1.08x0.95mm_HandSolder
C10: 2.2n; C_0603_1608Metric_Pad1.08x0.95mm_HandSolder
C11: 4.7p; C_0603_1608Metric_Pad1.08x0.95mm_HandSolder
C12: 1.5p; C_0603_1608Metric_Pad1.08x0.95mm_HandSolder
C13: 1.0p; C_0603_1608Metric_Pad1.08x0.95mm_HandSolder
C14, C15: 22p; C_0603_1608Metric_Pad1.08x0.95mm_HandSolder
C16: 10u; C_0603_1608Metric_Pad1.08x0.95mm_HandSolder
D1, D2: LED_Small; D_0603_1608Metric_Pad1.05x0.95mm_HandSolder
D3: LED; D_0603_1608Metric_Pad1.05x0.95mm_HandSolder
H1, H2, H3, H4: MountingHole_Pad; MountingHole_3.2mm_M3_DIN965_Pad
J1: Conn_01x07_Socket; JST_EH_B7B-EH-A_1x07_P2.50mm_Vertical
J2: Conn_02x07_Odd_Even; PinHeader_2x07_P1.27mm_Vertical_SMD
L1: 8.2n; L_0805_2012Metric_Pad1.05x1.20mm_HandSolder
L2: 3.9n; L_0805_2012Metric_Pad1.05x1.20mm_HandSolder
L3: 2.7n; L_0805_2012Metric_Pad1.05x1.20mm_HandSolder
Q1, Q2, Q3, Q4, Q5: 2N7002; SOT-23
R1: 22k; R_0603_1608Metric_Pad0.98x0.95mm_HandSolder
R2, R3, R4: 1k; R_0603_1608Metric_Pad0.98x0.95mm_HandSolder
R5, R7, R8, R9, R10, R11, R12, R13, R14, R15, R16: 10k; R_0603_1608Metric_Pad0.98x0.95mm_HandSolder
R6: 1M; R_0603_1608Metric_Pad0.98x0.95mm_HandSolder
SW2: SW_SPST; SW_SPST_B3S-1000
U1: STM32L412KBTx; LQFP-32_7x7mm_P0.8mm
U2: MIC5219-3.3YMM; MSOP-8_3x3mm_P0.65mm
U3: nRF24L01P; QFN-20-1EP_4x4mm_P0.5mm_EP2.5x2.5mm
Y1: 16MHz; Crystal_SMD_HC49-SD_HandSoldering

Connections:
+3.3V: C2.1, C3.1, C5.1, C6.1, C7.1, C8.1, C16.1, D3.2 (A), J2.3, Q1.1 (G), Q2.1 (G), Q3.1 (G), Q4.1 (G), Q5.1 (G), R7.1, R8.1, R9.1, R10.1, R11.1, SW2.2 (B), U1.1 (VDD), U1.5 (VDDA), U1.17 (VDD), U2.3 (OUT), U3.7 (VDD), U3.15 (VDD), U3.18 (VDD)
ANT1: L1.2, L3.1, U3.12 (ANT1)
ANT2: L1.1, L2.1, U3.13 (ANT2)
Appairing_Btn: R5.1, SW2.1 (A), U1.25 (PA15)
Chip_Enable: U1.15 (PB1), U3.1 (CE)
Data_Clock_SNES: J1.2, Q1.3 (D), R12.2
Data_Clock_STM32: Q1.2 (S), R7.2, U1.26 (PB3)
Data_Latch_SNES: J1.3, Q2.3 (D), R13.2
Data_Latch_STM32: Q2.2 (S), R8.2, U1.27 (PB4)
GND: C1.1, C2.2, C3.2, C4.2, C5.2, C6.2, C7.2, C8.2, C9.2, C10.2, C11.2, C13.1, C14.2, C15.2, C16.2, H1.1, H2.1, H3.1, H4.1, J1.7, J2.5, J2.7, J2.11, R1.2, R2.2, R3.2, R4.2, R5.2, U1.16 (VSS), U1.32 (VSS), U2.5 (GND), U2.6 (GND), U2.7 (GND), U2.8 (GND), U3.8 (VSS), U3.14 (VSS), U3.17 (VSS), U3.20 (VSS)
GND2: Antenna_nRF1.2 (GND)
IOBit_SNES: J1.6, Q5.3 (D), R16.2
IOBit_STM32: Q5.2 (S), R11.2, U1.30 (PB7)
NRST: C1.2, J2.6, U1.4 (NRST)
unnamed: C12.2, L2.2
unnamed: D1.1 (K), R2.1
unnamed: D2.1 (K), R3.1
unnamed: D3.1 (K), R4.1
unnamed: C4.1, U2.4 (BP)
unnamed: C9.1, U3.19 (DVDD)
unnamed: R1.1, U3.16 (IREF)
Player1_LED: D1.2 (A), U1.23 (PA13)
RF_Output: Antenna_nRF1.1 (Feed_point), C12.1, C13.2
SPI_Chip_Select: U1.14 (PB0), U3.2 (CSN)
SPI_Clock: U1.13 (PA7), U3.3 (SCK)
SPI_Digital_Input: U1.12 (PA6), U3.4 (MOSI)
SPI_Digital_Output: U1.11 (PA5), U3.5 (MISO)
SWDCK: J2.14, U1.8 (PA2)
SWDIO: J2.13, U1.9 (PA3)
Serial_Data1_SNES: J1.4, Q3.3 (D), R14.2
Serial_Data1_STM32: Q3.2 (S), R9.2, U1.28 (PB5)
Serial_Data2_SNES: J1.5, Q4.3 (D), R15.2
Serial_Data2_STM32: Q4.2 (S), R10.2, U1.29 (PB6)
Status_LED: D2.2 (A), U1.24 (PA14)
USART2_RX: J2.1, U1.3 (PC15)
USART2_TX: J2.2, U1.2 (PC14)
VDD_PA: C10.1, C11.1, L3.2, U3.11 (VDD_PA)
XC1: C14.1, R6.1, U3.10 (XC1), Y1.2
XC2: C15.1, R6.2, U3.9 (XC2), Y1.1

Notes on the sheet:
Mounting Holes
NRF24 Antenna
Antenna Module
SWD Connector
NES Port
Appairing Button
LEDs System
STM32-L412KBTx
MIC5219-3.3YMM 5 to 3.3
NRF24L01
NRF24 Crystal
Level Shifter

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
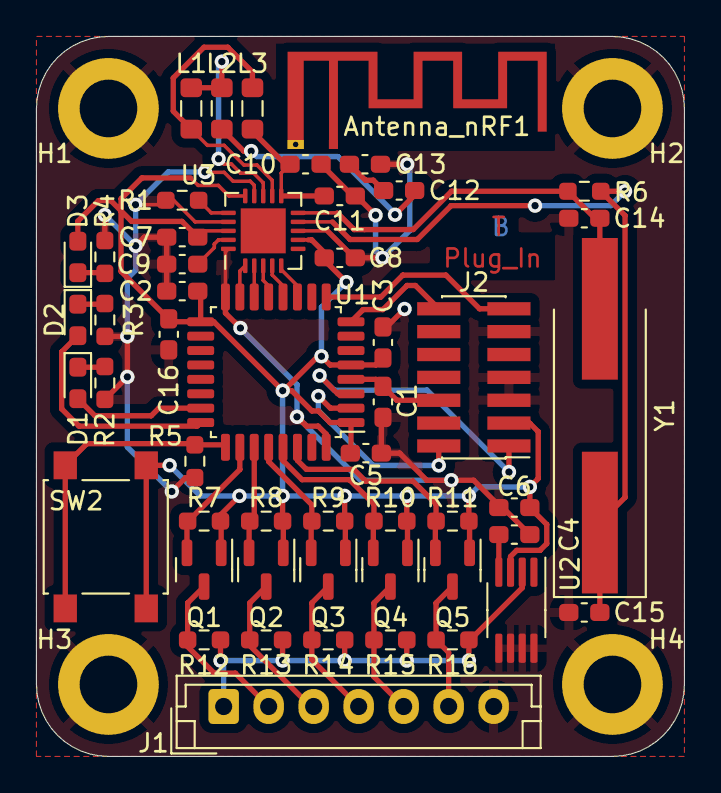
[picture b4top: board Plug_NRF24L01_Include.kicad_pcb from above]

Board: 2 copper layers, 36.0 x 40.0 mm, 55 parts (0 on the bottom side), 39 nets.

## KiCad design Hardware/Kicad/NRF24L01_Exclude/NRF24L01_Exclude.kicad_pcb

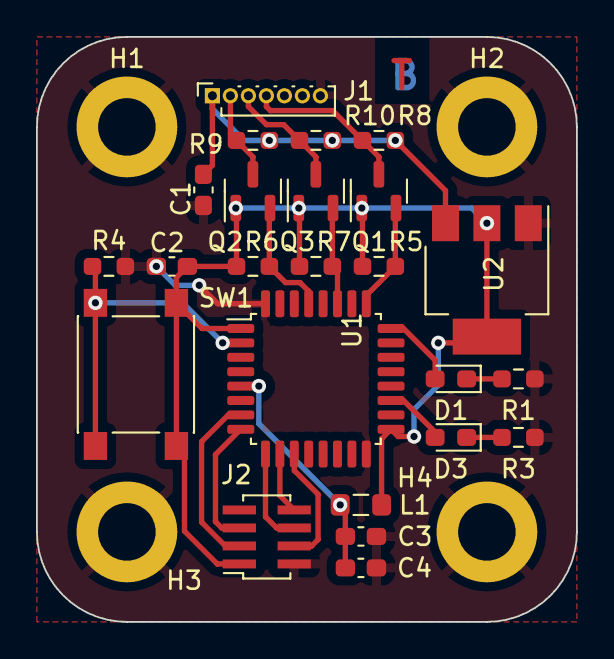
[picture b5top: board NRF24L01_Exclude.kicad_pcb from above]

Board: 2 copper layers, 30.0 x 32.5 mm, 28 parts (0 on the bottom side), 20 nets.

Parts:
C1, C2, C3: 1u; C_0603_1608Metric_Pad1.08x0.95mm_HandSolder
C4: 10n; C_0603_1608Metric_Pad1.08x0.95mm_HandSolder
D1, D3: LED_Small; D_0603_1608Metric_Pad1.05x0.95mm_HandSolder
H1, H2, H3, H4: MountingHole_Pad; MountingHole_3.2mm_M3_DIN965_Pad
J1: Conn_01x07_Socket; PinSocket_1x07_P1.00mm_Vertical
J2: Conn_01x08_Socket; PinSocket_2x04_P1.00mm_Vertical_SMD
L1: 39n; L_0805_2012Metric_Pad1.05x1.20mm_HandSolder
Q1, Q2, Q3: 2N7002; SOT-23
R1, R3: 1k; R_0603_1608Metric_Pad0.98x0.95mm_HandSolder
R4, R5, R6, R7, R8, R9, R10: 10k; R_0603_1608Metric_Pad0.98x0.95mm_HandSolder
SW1: SW_Push; SW_Push_1P1T_NO_6x6mm_H9.5mm
U1: STM32L412KBTx; LQFP-32_7x7mm_P0.8mm
U2: AMS1117-3.3; SOT-223-3_TabPin2

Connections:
+3.3V: C2.1, J2.1, L1.1, Q1.1 (G), Q2.1 (G), Q3.1 (G), R5.1, R6.1, R7.1, SW1.1, U1.1 (VDD), U1.17 (VDD), U2.2 (VO)
+3.3VA: C3.1, C4.1, L1.2, U1.5 (VDDA)
+5V: C1.1, J1.1, R8.1, R9.1, R10.1, U2.3 (VI)
Appairing_Btn: R4.1, SW1.2, U1.2 (PC14)
Chip_Enable: J2.4, U1.11 (PA5)
Data_Clock_SNES: J1.2, Q2.3 (D), R9.2
Data_Clock_STM32: Q2.2 (S), R6.2, U1.29 (PB6)
Data_Latch_SNES: J1.3, Q3.3 (D), R10.2
Data_Latch_STM32: Q3.2 (S), R7.2, U1.27 (PB4)
GND: C1.2, C2.2, C3.2, C4.2, H1.1, H2.1, H3.1, H4.1, J1.7, J2.2, R1.2, R3.2, R4.2, U1.16 (VSS), U1.32 (VSS), U2.1 (GND)
unnamed: D1.1 (K), R1.1
unnamed: D3.1 (K), R3.1
Player1_LED: D1.2 (A), U1.24 (PA14)
SPI_Chip_Select: J2.3, U1.7 (PA1)
SPI_Clock: J2.6, U1.9 (PA3)
SPI_Digital_Input: J2.5, U1.8 (PA2)
SPI_Digital_Output: J2.8, U1.10 (PA4)
Serial_Data_SNES: J1.4, Q1.3 (D), R8.2
Serial_Data_STM32: Q1.2 (S), R5.2, U1.25 (PA15)
Status_LED: D3.2 (A), U1.19 (PA9)
